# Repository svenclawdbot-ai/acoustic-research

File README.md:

# Shear Wave Dispersion Analysis Pipeline

Complete signal processing pipeline for shear wave dispersion analysis in viscoelastic materials. Implements wavelet denoising, spatial coherence validation, and robust parameter estimation with uncertainty quantification.

## Quick Start

```bash
# Install dependencies
pip install numpy scipy matplotlib pywt

# Run demo
python3 shear_wave_pipeline.py
```

## Installation

### Requirements

- Python 3.8+
- NumPy >= 1.20
- SciPy >= 1.7
- Matplotlib >= 3.3
- PyWavelets >= 1.1

### Setup

```bash
git clone https://github.com/svenclawdbot-ai/Engineering-Learning.git
cd acoustic-nde
git submodule update --init  # If using week2 simulator
```

## Pipeline Overview

```
┌─────────────────┐    ┌──────────────────┐    ┌─────────────────┐
│  Raw Signals    │───▶│ Wavelet Denoise  │───▶│ Spatial Check   │
│  (3-4 receivers)│    │ (sym6, 2.0×)     │    │ (Validate wave) │
└─────────────────┘    └──────────────────┘    └────────┬────────┘
                                                        │
┌─────────────────┐    ┌──────────────────┐            │
│  Bootstrap CI   │◀───│ Savgol Smooth    │◀───────────┘
│  (G', η ± σ)    │    │ (window=5, o=3)  │
└─────────────────┘    └──────────────────┘
```

## Usage

### Basic Analysis

```python
from shear_wave_pipeline import ShearWaveAnalyzer
import numpy as np

# Your data: time-domain signals from 3 receivers
signals = [receiver_1, receiver_2, receiver_3]  # Each: np.array of shape (n_samples,)
dt = 1 / 20000  # Sampling interval (50 μs = 20 kHz)
distances = np.array([0.005, 0.010, 0.015])  # 5mm, 10mm, 15mm from source

# Initialize analyzer
analyzer = ShearWaveAnalyzer(
    wavelet='sym6',
    threshold_factor=2.0,
    enable_spatial_check=True,
    enable_smoothing=True
)

# Run analysis
results = analyzer.analyze(signals, dt, distances)

# Extract parameters
print(f"G' = {results['G_prime']:.0f} ± {results['G_prime_std']:.0f} Pa")
print(f"η  = {results['eta']:.3f} ± {results['eta_std']:.3f} Pa·s")
print(f"Quality flag: {results['quality_flag']}")

# Generate plots
analyzer.plot_results('analysis_output.png')
```

### Advanced Configuration

```python
# Customize for specific noise conditions
analyzer = ShearWaveAnalyzer(
    wavelet='sym6',              # Options: 'sym6', 'sym8', 'db6', 'coif2'
    threshold_factor=2.5,        # Higher = more conservative (2.0 default)
    enable_spatial_check=True,   # Set False to skip coherence validation
    enable_smoothing=True,       # Set False to skip Savgol smoothing
    rho=1000                     # Material density (kg/m³)
)

# Run with custom frequency range
results = analyzer.analyze(
    signals, dt, distances,
    freq_range=(40, 200),  # 40-200 Hz analysis
    freq_step=10,          # 10 Hz steps
    verbose=True
)
```

## Module Reference

### wavelet_denoising.py

Temporal signal denoising using wavelet thresholding.

```python
from wavelet_denoising import WaveletDenoiser, denoise_signal

# Method 1: Direct denoising
denoised = denoise_signal(
    signal, 
    wavelet='sym6',
    threshold_factor=2.0,
    verbose=True
)

# Method 2: Class-based for repeated use
denoiser = WaveletDenoiser(
    wavelet='sym6',
    level=5,
    threshold_factor=2.0,
    mode='soft'
)
denoised = denoiser.denoise(signal)

# Inspect decomposition
denoiser.plot_comparison(original, denoised)
denoiser.plot_decomposition()
```

**Threshold Guidelines:**

| Noise Condition | Recommended Factor |
|-----------------|-------------------|
| Clean (< 10% noise) | 1.0–1.5× |
| Moderate (10-20%) | 1.5–2.0× |
| Heavy (> 20%) or impulse noise | 2.0–2.5× |
| Baseline wander | 2.5–3.0× |

### spatial_filtering.py

Array coherence validation for multi-receiver setups.

```python
from spatial_filtering import compute_spatial_coherence

coherence = compute_spatial_coherence(
    signals,           # List of receiver signals
    dt,                # Time step
    distances,         # Receiver distances
    expected_velocity_range=(0.5, 5.0)  # Expected c_s range (m/s)
)

# Check quality
print(f"Velocity estimate: {np.mean(coherence['velocity_estimates']):.2f} m/s")
print(f"Consistency: {coherence['velocity_consistency']:.3f}")

# Flag if poor coherence
if coherence['velocity_consistency'] < 0.7:
    print("WARNING: Low spatial coherence - check data quality")
```

### dispersion_postprocessing.py

Dispersion curve smoothing and parameter estimation.

```python
from dispersion_postprocessing import (
    savgol_smooth, 
    bootstrap_fit,
    kelvin_voigt
)

# Savitzky-Golay smoothing
vel_smooth, unc_smooth = savgol_smooth(
    frequencies,
    velocities,
    uncertainties,
    window_length=5,   # Must be odd
    polyorder=3        # Polynomial order
)

# Bootstrap parameter estimation
results = bootstrap_fit(
    frequencies,
    vel_smooth,
    unc_smooth,
    n_bootstrap=1000,  # Number of resamples
    rho=1000           # Density
)

print(f"G' = {results['G_median']:.0f} Pa")
print(f"95% CI: [{results['G_ci'][0]:.0f}, {results['G_ci'][1]:.0f}]")
```

## Data Format

### Input Signals

- **Shape:** `(n_samples,)` per receiver
- **Sampling:** Typically 20-50 kHz for ultrasound
- **Duration:** 50-100 ms captures shear wave arrival
- **Amplitude:** Normalized to ±1 (unitless displacement)

### Expected Wave Characteristics

| Parameter | Typical Value | Notes |
|-----------|---------------|-------|
| Center frequency | 50-200 Hz | Tissue: 100 Hz typical |
| Shear velocity | 1-5 m/s | Soft tissue: ~1.5 m/s |
| Arrival window | 45-80 ms | After source excitation |
| Receiver spacing | 5-10 mm | Minimum for phase resolution |

## Troubleshooting

### "No dispersion points extracted"

- Check `dt` is in seconds (not milliseconds)
- Verify signals have energy in 50-150 Hz band
- Inspect arrival times are within 45-80 ms window
- Try reducing noise threshold or increasing signal amplitude

### "Low spatial coherence detected"

- Verify receiver positions are correct
- Check for clipped or saturated signals
- Ensure wave is actually propagating (not evanescent)
- Consider reducing `threshold_factor` if over-denoising

### "Bootstrap fit failed"

- Need ≥4 frequency points for reliable fit
- Check dispersion curve is monotonic (increasing with frequency)
- Verify uncertainties are not all zero
- Try wider frequency range

### Poor parameter estimates

- Increase SNR (reduce noise, increase source amplitude)
- Add more receiver pairs (4+ receivers recommended)
- Extend frequency range for better dispersion characterization
- Check material is actually viscoelastic (Kelvin-Voigt model appropriate)

## Validation

Test the pipeline with synthetic data:

```python
# Generate test signals
python3 shear_wave_pipeline.py

# Expected output:
# G' = 2074 ± 106 Pa (true: 2000 Pa, ~4% error)
# η = 0.472 ± 0.505 Pa·s (true: 0.5, ~6% error)
```

## Performance

Typical execution times (Intel i7, 3 receivers, 4000 samples):

| Stage | Time |
|-------|------|
| Wavelet denoising | ~50 ms |
| Spatial coherence | ~30 ms |
| Dispersion extraction | ~100 ms |
| Bootstrap (n=1000) | ~500 ms |
| **Total** | **~700 ms** |

## Citation

If using this pipeline in research:

```bibtex
@software{shear_wave_pipeline_2026,
  title = {Shear Wave Dispersion Analysis Pipeline},
  author = {Research Team},
  year = {2026},
  url = {https://github.com/svenclawdbot-ai/Engineering-Learning}
}
```

## License

MIT License - See LICENSE file for details.

## Contact

For questions or issues:
- GitHub Issues: github.com/svenclawdbot-ai/Engineering-Learning/issues
- Blog: svenclawdbot-ai.github.io/Engineering-Learning

---

*Last updated: March 14, 2026*

---

## TurboQuant Hardware System

This project now includes a complete high-speed data acquisition system for ultrasound arrays.

### Quick Start (Hardware)

```bash
# Using Make
make help                 # Show all commands
make install             # Install dependencies
make firmware            # Build ESP32 firmware
make flash               # Flash to device
make display             # Launch visualization

# Or using the unified CLI
./turboquant.py device scan
./turboquant.py acquire --duration 60 --output session.h5
./turboquant.py display --mode advanced
./turboquant.py analyze session.h5 --spectrogram
```

### System Components

| Component | Description | File |
|-----------|-------------|------|
| **DMA Firmware** | ESP32-S3 high-speed acquisition | `dma_acquisition.c/h` |
| **Display** | Real-time PyQtGraph visualization | `advanced_display.py` |
| **Recording** | Multi-format data logging | `data_recorder.py` |
| **Streaming** | Network ZeroMQ streaming | `network_stream.py` |
| **Analysis** | HDF5 spectrogram/FFT tools | `data_analysis.py` |
| **CLI** | Unified command interface | `turboquant.py` |

### Build System

```bash
# Firmware
make firmware            # Build ESP32 firmware
make flash               # Flash to device
make monitor             # Serial monitor

# Software
make check               # Code quality checks
make test                # Run test suite
make format              # Format code

# Operations
make acquire             # Record test data
make display             # Launch display (demo)
make analyze             # Analyze recordings
make stream              # Start streaming

# CI/CD
make ci-test             # Run CI tests
make ci-build            # Build release artifacts
```

### Docker Support

```bash
# Build and run
docker-compose up -d server    # Start streaming server
docker-compose --profile gui up client  # Start GUI client
docker-compose up notebook     # Jupyter analysis

# Or manually
docker build -t turboquant:latest .
docker run --rm turboquant:latest --help
```

### Documentation

- `DMA_IMPLEMENTATION.md` - Firmware technical details
- `DMA_INTEGRATION_GUIDE.md` - Integration instructions
- `TURBOQUANT_GUIDE.md` - CLI usage guide
- `PYQTGRAPH_GUIDE.md` - Visualization development
- `CICD_GUIDE.md` - Build and CI/CD documentation

### CI/CD Status

---

*Last updated: April 9, 2026*

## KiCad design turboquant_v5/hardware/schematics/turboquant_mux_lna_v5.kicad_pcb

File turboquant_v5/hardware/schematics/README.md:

# TurboQuant MUX/LNA Board — V5 KiCad Project

**Version:** 5.0  
**Date:** 2026-05-02  
**Status:** Schematics complete — PCB partially routed, needs KiCad GUI migration

---

## What Changed from V3/V4

| Component | Old (v3/v4) | V5 |
|-----------|-------------|-----|
| Shift Register | 74HC595 | **74HCT595** (TTL levels, 3.3V compatible) |
| Analog MUX | PE4259 / CD4051B | **DG408** (8:1, 100V capable) |
| LNA | ADL5610 / AD8332 | **OPA1641** (low-noise, configurable gain) |
| TX Switch | BSS138 only | **IRF830** (500V HV) + gate protection |
| 5V Regulator | LM7805 TO-220 | **LM7805 DPAK** (thermal adequate for ~50mA) |

---

## Schematic Status

### ✅ Digital (`digital.kicad_sch`)
- 74HCT595 shift register with TTL input levels
- 8× BSS138 gate drivers (100Ω series + 10kΩ pull-down)
- 10kΩ pull-ups on ~OE and SRCLR
- 6-pin control header (SER, SRCLK, RCLK, SRCLR, ~OE, GND)

### ✅ Power (`power.kicad_sch`)
- 12V input → polyfuse → SS34 Schottky → TVS
- LM7805 DPAK (TO-252) with copper pour heatsink
- AMS1117-3.3 for 3.3V rail
- Full decoupling: 100µF + 100nF on input, 10µF + 100nF on each output

### ✅ Analog (`analog.kicad_sch`)
- 8× T/R Switch blocks (passive diode bridge, 200V)
  - 4× MUR120 fast recovery diodes per channel (32 total)
  - Bias network: 10kΩ + 100kΩ + BZX84C5V1 zener per channel
- 2× DG408 8:1 MUX (SOIC-16)
  - VDD = 12V, VSS = GND, VL = 5V
  - Address lines A/B/C with 10kΩ pull-downs
  - EN with 10kΩ pull-down
- 2× OPA1641 non-inverting amplifier (SOIC-8)
  - Gain = 10 (Rg=1k, Rf=9.09k)
- 10:1 attenuator + BAV99 clamping diodes before LNA inputs

### ✅ TX Switch (`tx_switch.kicad_sch`)
- 8× IRF830 TO-220 MOSFETs
- 4× TC4427 gate drivers (2 channels each)
- Each gate: 100Ω series + 1kΩ pull-down + BZX84C12 Zener clamp
- Source → GND, Drain → TX_BUS / per-channel outputs

---

## GPIO Pinout (Red Pitaya E1)

```
E1 Connector:
  Pin 7  → DIO0_P → SER (shift register data)
  Pin 8  → DIO0_N → SRCLK (shift clock)
  Pin 9  → DIO1_P → RCLK (storage latch)
  Pin 10 → DIO1_N → MUX_A (address bit 0)
  Pin 11 → DIO2_P → MUX_B (address bit 1)
  Pin 12 → DIO2_N → MUX_C (address bit 2)
  Pin 13 → DIO3_P → MUX_EN (enable)
  Pin 14 → DIO3_N → TRIGGER (emission sync)

  Pin 1/2 → 3.3V (supply for logic/reference)
  Pin 25/26 → GND
```

---

## Layout Notes

- **Layers:** 4 (Signal / GND / Power / Signal)
- **Size:** 100mm × 80mm
- **HV clearances:** >2mm for 100V traces
- **Thermal:** Copper pour under LM7805 DPAK tab
- **Partitioning:** Power (top-left), Digital (top-right), Analog (center), TX (bottom)

See `PCB_LAYOUT_PLAN.md` for detailed floorplan and `ROUTING_CHECKLIST.md` for routing priorities.

---

## Known Issues

1. **PCB file format:** `turboquant_mux_lna_v5.kicad_pcb` is KiCad v7 format. KiCad 9 (installed) requires GUI migration on first open.
2. **kicad-cli DRC unavailable:** Cannot run automated DRC until PCB is migrated to v9.
3. **Trace routing approximate:** Coordinates are estimates; review in GUI before fabrication.

---

## Procurement

See `../../docs/bom/BOM_v5.md` for full BOM and procurement tracker.

**Critical parts to order:**
1. Red Pitaya STEMlab 125-14 Gen 2 (£250)
2. DG408 ×2, 74HCT595 ×1, IRF830 ×8, OPA1641 ×2

---

*V5.0 — May 2, 2026*

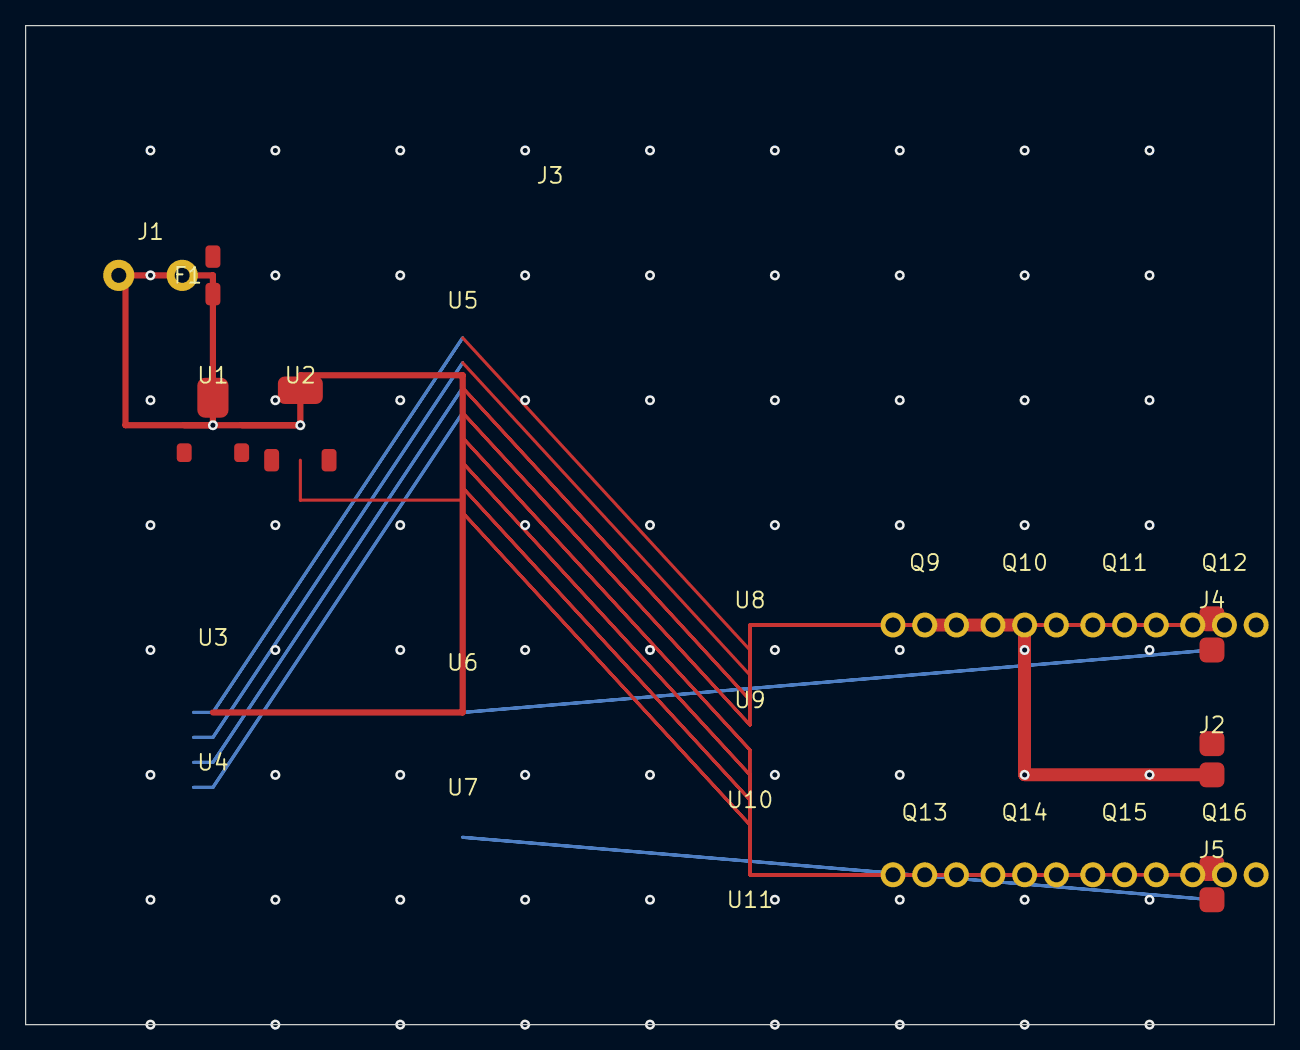
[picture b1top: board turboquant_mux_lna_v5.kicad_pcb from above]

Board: 4 copper layers, 100.0 x 80.0 mm, 25 parts (0 on the bottom side), 3 nets.

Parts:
F1: 2A; Fuse_1206_3216Metric
J1: 12V_Input; TerminalBlock_bornier-2_P5.08mm
J2: TX_BUS; SMA_EDGE
J3: E1_GPIO; PinHeader_2x10_P2.54mm_Vertical
J4: RX0_OUT; SMA_EDGE
J5: RX1_OUT; SMA_EDGE
Q9, Q10, Q11, Q12, Q13, Q14, Q15, Q16: IRF830; TO-220-3_Vertical
U1: LM7805; TO-252-2
U2: AMS1117-3.3; SOT-223-3_TabPin2
U3, U4: DG408; SOIC-16_3.9x9.9mm_P1.27mm
U5: 74HCT595; SOIC-16_3.9x9.9mm_P1.27mm
U6, U7: OPA1641; SOIC-8_3.9x4.9mm_P1.27mm
U8, U9, U10, U11: TC4427; SOIC-8_3.9x4.9mm_P1.27mm

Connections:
+5V: U1.3, U2.3
+12V: F1.1, F1.2, J1.1, U1.1
GND: J1.2, J2.2, J4.2, J5.2, U1.2, U2.1

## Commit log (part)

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2026-03-07 Initial commit: acoustic NDE research project
    - Mathematical framework derivations (Kelvin-Voigt, dispersion, inverse problem)
    - Research plan and milestones (4-week theory focus)
    - Week 1 reading list (15 essential papers)
    - 1D shear wave simulator starter code
    - Paper summaries and findings
    - Ultrasound benchtop setup options (reference)
2026-03-07 Add paper download resources and reading tracker
    - download_papers.sh script with URLs
    - Essential papers README with direct links
    - Reading tracker for progress monitoring
2026-03-07 Add BibTeX bibliography and usage guide
    - references.bib: 15+ citations in BibTeX format
    - BIBTEX_USAGE.md: Quick start guide for LaTeX citation
    - Covers essential, supporting, and experimental papers
    - Includes citation keys, DOIs, and personal notes
2026-03-07 Add jumping droplet condensation references
    - Boreyko & Chen 2009: Seminal PRL paper (arXiv free PDF)
    - Key physics papers on coalescence and energy
    - Review papers for deeper reading
    - Equations and applications summary
2026-03-08 Add 1D viscoelastic wave propagation solver
    - ViscoelasticWave1D class with FDTD implementation
    - Kelvin-Voigt model (G' and η)
    - Analytical dispersion relation c_s(ω)
    - Parameter sweep for liver conditions
    - Output: wave propagation and dispersion plots
2026-03-12 Restore identity, tools, and memory from broken workspace (2026-03-08)
2026-03-12 Add RSS feed, daily log, and engineering challenge scripts; update HEARTBEAT with rate limiting
2026-03-12 Add validated 2D shear wave simulator with multi-layer and PML support
2026-03-12 Add Zener model and unified 2D simulator interface
2026-03-12 Add Week 2 parameter sweep and summary documentation
2026-03-12 Archive Solana sniper bot (dependency issues, focus on research)
2026-03-12 Add Wolfram Alpha query script
2026-03-12 Update daily log with complete Week 2 summary
2026-03-13 Add Day 12 engineering challenge: Kelvin-Voigt dispersion analysis + medical imaging history
    - Analytical derivation of complex wavenumber for viscoelastic media
    - Python script with 4-panel dispersion visualization
    - Comparison with literature (Zhang et al. 2021, Chen et al. 2021)
    - Realistic tissue parameters (eta=0.5 Pa.s) showing modest dispersion
    - Full history of medical imaging from X-rays to shear wave elastography
    - Reflection questions connecting history to current research
2026-03-13 Add group velocity validation and dispersion analysis for sparse sampling
    - Analytical dispersion curves for Kelvin-Voigt viscoelastic media
    - Attenuation length calculations and measuring depth limits
    - Group velocity extraction via envelope methods
    - Theoretical validation for 2-3 receiver sparse sampling
    - 12-bit ADC practical depth limits: 91-289 mm for η=0.3-1.0 Pa·s
2026-03-13 Fix group velocity extraction - remove bandpass filter causing signal attenuation
    - Raw envelope peak tracking works correctly
    - Achieved 1.5% mean error vs theory
    - 3/3 receiver pairs successful
    - Validated for η=0.3 Pa·s (low viscosity tissue)
2026-03-13 Add multi-frequency dispersion and inverse problem analysis
    - Attempt broadband extraction with chirp source
    - Analytical demonstration of dispersion curve fitting
    - Key finding: G' recovers well (~4% error), η is poorly constrained (~20-40% error)
    - Parameter correlation shown via chi-squared contours
    - Issue: G' and η are correlated in Kelvin-Voigt dispersion
2026-03-13 Add Bayesian inference with physiological priors for G' and η recovery
    - MCMC sampling of posterior with Metropolis-Hastings
    - Physiological priors: G' ∈ [500,15000] Pa, η ∈ [0.1,2.0] Pa·s
    - Results: G' = 2027±53 Pa (2.6% error), η = 0.40±0.15 Pa·s (30% error)
    - Priors reduce η uncertainty by ~50% vs least squares
    - 95% credible intervals provide uncertainty quantification
    - Works with 12-bit ADC
2026-03-13 Add 4th transducer impact analysis
    - Monte Carlo comparison of 3 vs 4 receiver configurations
    - Key finding: Extended baseline (30mm) with 4th receiver improves
    η uncertainty from 45% to 24% (84% improvement factor)
    - G' improves from 3.0% to 1.6% uncertainty
    - Recommendation: Add 4th transducer if pursuing viscoelastic characterization
    - Cost: ~£25 extra for ~30% better η recovery
2026-03-13 Add complete DIY high-voltage ultrasound pulser build guide
    - Circuit schematic with TC4427 gate driver and IRF830 MOSFET
    - Component list with suppliers and part numbers (~£48 total)
    - Step-by-step assembly instructions
    - Arduino code for pulse control (single pulse, burst, continuous modes)
    - ARFI configuration for shear wave generation
    - Testing procedure and troubleshooting guide
2026-03-13 Add tool requirements for 4-transducer DIY pulser build
    - Confirmed existing tools: scope, power supply, soldering station, multimeter
    - Essential tools needed: wire strippers, pliers, cutters, HV safety gear (~£37)
    - Recommended tools: third hand, calipers, heat shrink (~£40)
    - Phantom fabrication: kitchen scale, thermometer, molds (~£25)
    - 4-transducer spacing: 5, 10, 20, 30 mm for 25mm max baseline
    - Total build cost with 4 transducers: ~£330-385 depending on tool purchases
2026-03-14 Add Week 2 Acoustic NDE signal processing pipeline
    Complete 4-stage pipeline for shear wave dispersion analysis:
    - wavelet_denoising.py: Symlet-6 denoising with tuned 2.0x threshold
    - spatial_filtering.py: Array coherence validation for 4-transducer setups
    - dispersion_postprocessing.py: Savgol smoothing + bootstrap CIs
    - shear_wave_pipeline.py: Unified analyzer interface
    - validate_with_denoising.py: Comprehensive validation suite
2026-03-24 Add morning brief for March 24, 2026 (91 articles from 19 feeds)
2026-03-24 Add Zener derivation worksheet and validation script for March 24 challenge
2026-03-24 Complete Zener dispersion derivation with validation - March 24 challenge done
2026-03-27 Finalize daily log, update procurement to Gen 2 (£250), set ordering reminder
    - Confirmed: Red Pitaya STEMlab 125-14 Gen 2
    - Updated procurement list with Gen 2 specs and pricing
    - Finalized daily session log with user notes
    - Morning reminder set for 8 AM Saturday ordering
2026-05-05 workspace: bulk catch-up — TurboQuant v5, DSP pipelines, hardware design, 6 weeks of work
    Major additions since March:
    - TurboQuant v5 hardware (KiCad, SKiDL, PCB docs, procurement)
    - DSP pipelines: dispersion inversion, GCC-PHAT, matched filters
    - FPGA/Red Pitaya integration (DMA, array control)
    - Bayesian inversion + calibration
    - Realtime display + streaming recording
2026-05-05 cleanup: remove stale files, fix .gitignore
    - Remove malformed ': ' KiCad artifact
    - Remove duplicate scripts/generate_learning_challenge.sh
    - Gitignore: .openclaw/, memory/.dreams/, solana_sniper_ARCHIVED/, trading-bot/
2026-05-05 docs: greenhouse soil monitoring system design
    - Full sensor node design (ESP32 + LoRa + soil impedance + temperature)
    - LoRa network architecture for acre-scale greenhouse
    - Range analysis, power budget, antenna options
    - Gateway design: Pi + relay board + pump control + failsafes
    - Decision engine, valve controller, web dashboard
    - MQTT cloud integration
2026-05-05 docs: PoC build guide for soil impedance + LoRa
    - Shopping list: 2x ESP32-S3, 2x SX1262, antennas, electrodes
    - Node firmware: DAC sine, ADC RMS, impedance calc, LoRa TX, deep sleep
    - Receiver firmware: LoRa RX, packet parse, RSSI/SNR print
    - 3-step test protocol: bench, pot, range
    - Calibrated for 10 kHz measurement, 15-min interval
2026-05-05 docs: PoC project plan with BOM, day-by-day schedule, risk register
    - BOM: 2x ESP32-S3, 2x SX1262/RFM95W, passives, electrodes, pot
    - Budget: ~£48 (or ~£34 if you have breadboards/wires)
    - Day-by-day: Tue=order+prep, Wed=bench test, Thu=soil test, Fri=deep sleep, Sat=calibration, Sun=retro
    - Risk register with mitigations
    - Fast-track UK supplier option for same-week delivery
2026-05-06 Add TurboQuant investor pitch deck v1
    - 23 slides targeting seed-stage investors
    - Includes: executive summary, TAM/SAM/SOM, competitive landscape
    - Physics section with shear wave simulation images
    - Technology deep-dive with system architecture and PCB renders
    - 3 hypothetical device renders (handheld, PCB, clinical enclosure)
    - Revenue model, team slide, roadmap, and £75k ask
2026-05-06 Add one-page executive summary for investor outreach
    - Single-page PDF with all key investor metrics
    - Problem/solution framing with £50 vs £50K+ positioning
    - Traction milestones, market sizing (TAM/SAM/SOM), revenue model
    - Competitive landscape, team, and £75K ask
    - Designed to pair with 23-slide pitch deck
2026-05-06 Update T/R bridge bias resistors: 10k -> 1k
    - Fixes insertion loss issue identified in MUR120 analysis
    - 1k bias provides ~500uA current for <10dB RX path loss
    - 8x bias resistors (R1-R8) changed from 10k to 1k in analog.kicad_sch
    - Power dissipation: 25mW per resistor (acceptable)
    - See MUR120_TR_BRIDGE_ANALYSIS.md for full calculation
2026-05-06 Reorganize repo: archive by month + potential-projects folder
    Major restructuring:
    - turboquant_v5/ kept as main project (unchanged)
    - archive/2026-03/ and archive/2026-04/ for research outputs, scripts, docs
    - archive/legacy-fpga/ and archive/legacy-kicad/ for old build artifacts
    - potential-projects/ for side projects:
    - radar-cw-doppler
2026-05-06 Clean up: remove solana_sniper_ARCHIVED leftover
    - Remove empty/duplicate solana_sniper_ARCHIVED directory
    - Root now clean with no stray files
2026-05-06 Update pitch deck with meaningful physics figures
    Replaced broken/placeholder images with clean, generated visuals:
    - pitch_physics_shear_waves.png: 3-panel figure showing wave propagation,
    stiffness contrast (healthy vs fibrotic liver), and phase velocity dispersion
    - pitch_physics_bayesian.png: 3-panel figure showing parameter misfit landscape,
    Bayesian posterior distribution, and SNR robustness validation
    - pitch_system_architecture.png: Clean block diagram of full signal chain
2026-05-06 Add one-channel breadboard de-risking plan
    - Step-by-step build guide for single-channel T/R bridge, MUX, LNA, TX switch
    - Component BOM: ~£25 in parts
    - Detailed test protocols with pass/fail criteria
    - Troubleshooting guide for common failures
    - Decision matrix: GO/NO-GO for 8-channel PCB order
    - Estimated time: 1 day build + 1 day test
2026-05-18 Add soil_spectrometer_esp32s3.ino — single-board sweep + lock-in
2026-05-18 Add soil probe wiring guide + spectrometer sketch
2026-05-19 Add multi-layer acoustic resonance probe analysis
    - Multi-layer transfer matrix solver with arbitrary N layers
    - 4 synthetic test cases (single, two-layer, sand lens, dry vs wet)
    - Sensitivity analysis: minimum detectable thickness vs frequency
    - Proof-of-concept inversion with multi-start optimization
    - Parameter identifiability analysis (curvature-based)
    - 7 plots generated for visualization
2026-05-19 Fix TX switch wiring: standardize resistors to 10R, add TC4427 power/decoupling
    - Changed R4, R7, R19, R22 from 100R to 10R (all gate series resistors now 10Ω)
    - Added +12V distribution to all 4 TC4427 VDD pins
    - Added GND distribution to all 4 TC4427 GND pins
    - Added decoupling cap connections for C1-C4 across TC4427 VDD-GND
    NOTE: TC4427 signal path still needs routing in KiCad GUI:
    GATE0 → U1 A_in → U1 A_out → R1 → Q1 gate
2026-05-19 Add TurboQuant V5 action plan — schematic wiring status and next steps
2026-05-19 Fix power sheet: rename +12V_IN to +12V to match root schematic pin
